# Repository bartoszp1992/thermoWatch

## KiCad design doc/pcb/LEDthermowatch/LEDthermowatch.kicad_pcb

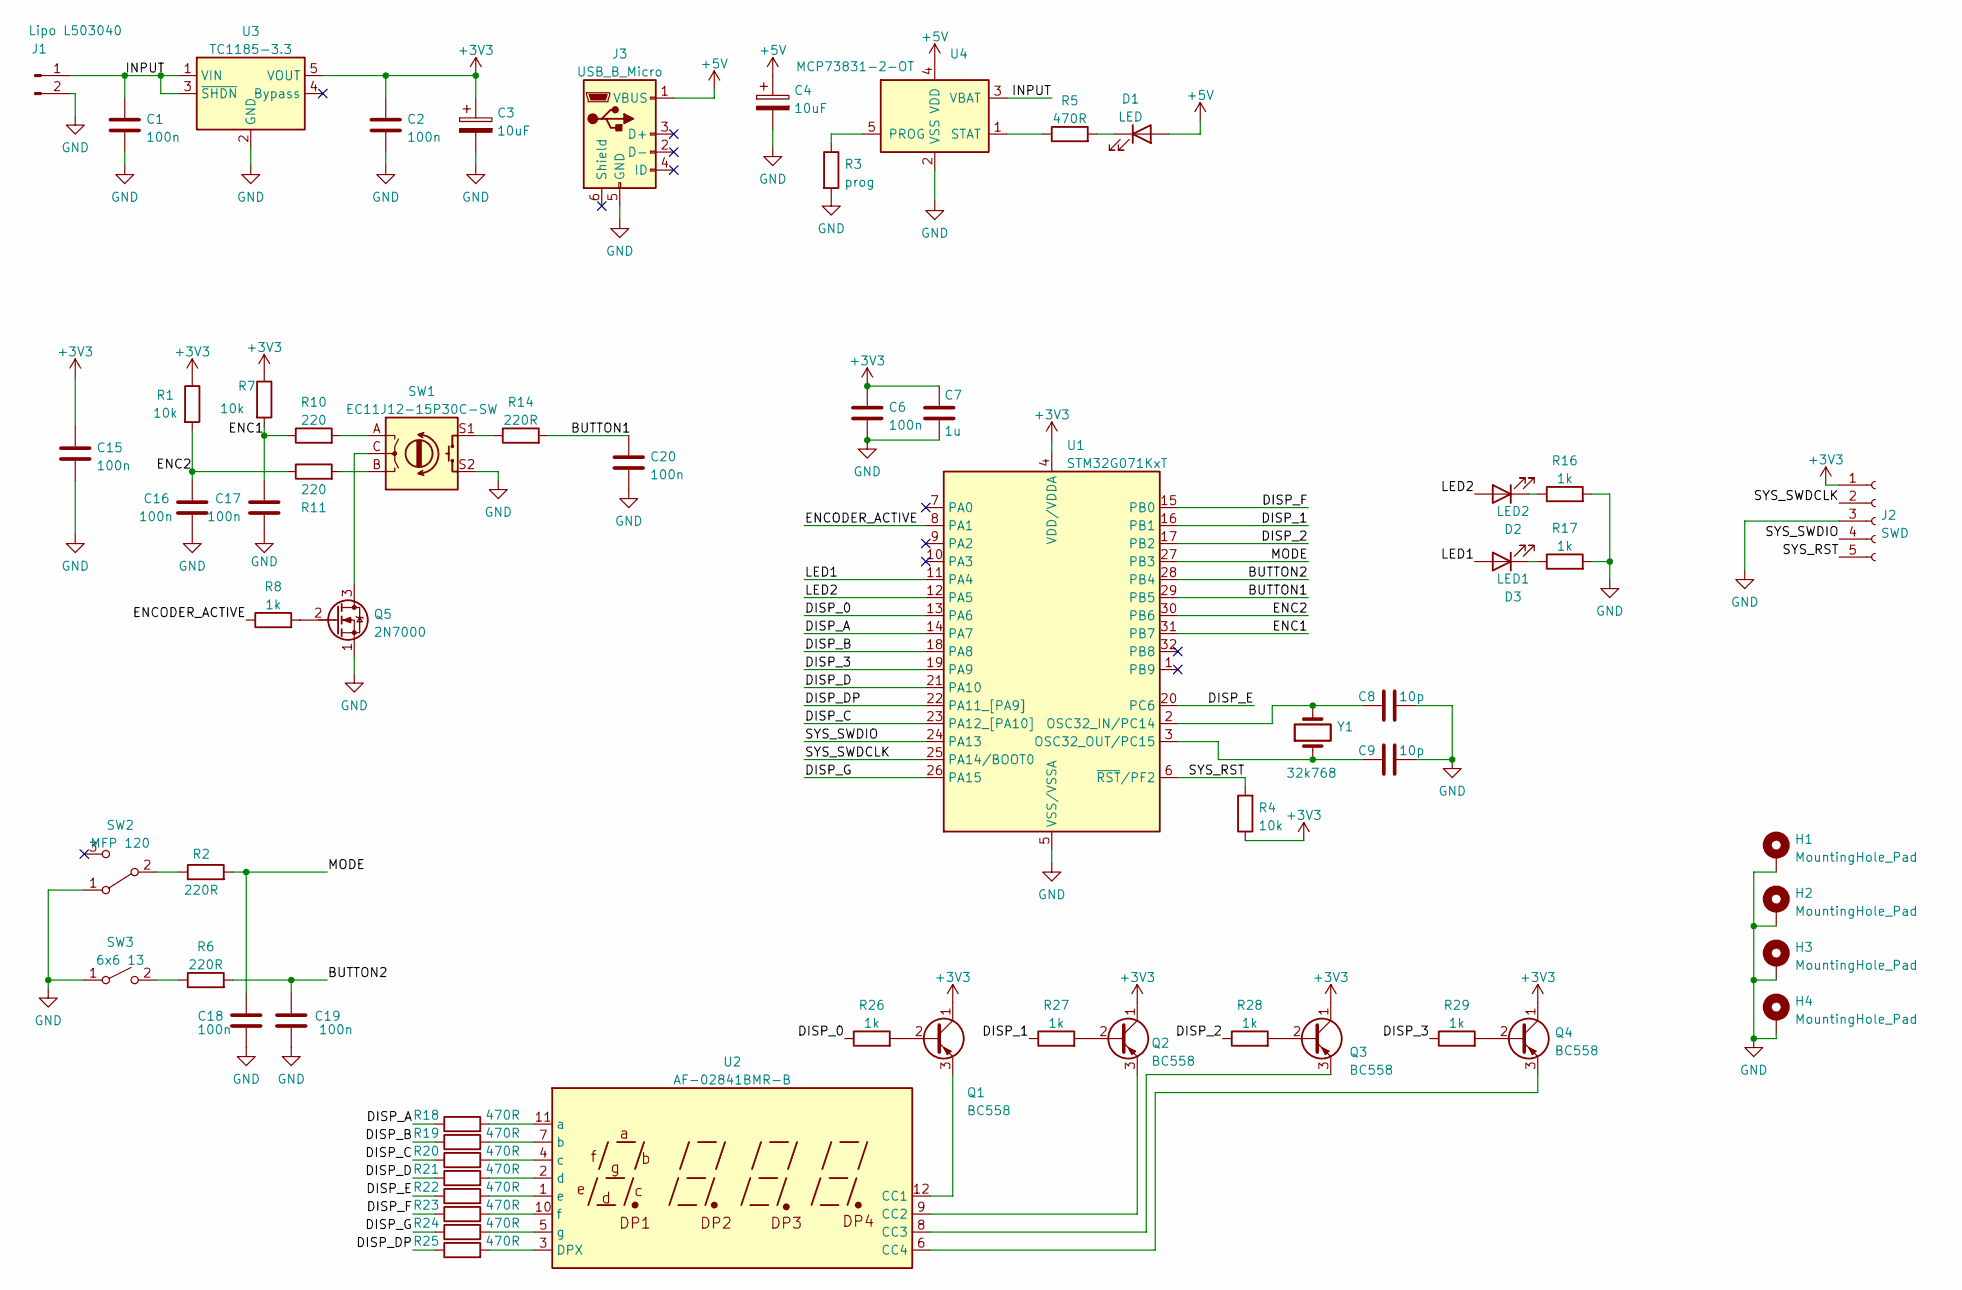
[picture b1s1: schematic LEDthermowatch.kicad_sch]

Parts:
C1, C2, C6, C15, C16, C17, C18, C19, C20: 100n; C_0805_2012Metric
C3, C4: 10uF; CP_Radial_D6.3mm_P2.50mm
C7: 1u; CP_Radial_D6.3mm_P2.50mm
C8, C9: 10p; C_0805_2012Metric
D1: LED; LED_0805_2012Metric
D2: LED2; LED_0805_2012Metric
D3: LED1; LED_0805_2012Metric
H1, H2, H3, H4: MountingHole_Pad; WirePad 4mm^2 Rect
J1: Lipo L503040; CELLEVIA 30x40mm
J2: SWD; PinHeader_1x05_P2.54mm_Vertical
J3: USB_B_Micro; USB_Micro-B_Molex_47346-0001
Q1, Q2, Q3, Q4: BC558; TO-92
Q5: 2N7000; TO-92
R1, R4, R7: 10k; R_Axial_DIN0207_L6.3mm_D2.5mm_P10.16mm_Horizontal
R2, R6, R14: 220R; R_Axial_DIN0207_L6.3mm_D2.5mm_P10.16mm_Horizontal
R3: prog; R_Axial_DIN0207_L6.3mm_D2.5mm_P10.16mm_Horizontal
R5: 470R; R_Axial_DIN0207_L6.3mm_D2.5mm_P10.16mm_Horizontal
R8, R16, R17, R26, R27, R28, R29: 1k; R_Axial_DIN0207_L6.3mm_D2.5mm_P10.16mm_Horizontal
R10, R11: 220; R_Axial_DIN0207_L6.3mm_D2.5mm_P10.16mm_Horizontal
R18, R19, R20, R21, R22, R23, R24, R25: 470R; R_0805_2012Metric
SW1: EC11J12-15P30C-SW
SW2: MFP 120
SW3: 6x6 13; SW_PUSH_6mm_H13mm
U1: STM32G071KxT; LQFP-32_7x7mm_P0.8mm
U2: AF-02841BMR-B; LED 14.2mm
U3: TC1185-3.3; SOT-23-5
U4: MCP73831-2-OT; SOT-23-5
Y1: 32k768; Crystal_D2.00mm_L6.00mm

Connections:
+3V3: C2.1, C3.1, C6.1, C7.1, C15.1, J2.1, Q1.1 (C), Q2.1 (C), Q3.1 (C), Q4.1 (C), R1.1, R4.1, R7.1, U1.4 (VDD/VDDA), U3.5 (VOUT)
+5V: C4.1, D1.2 (A), J3.1 (VBUS), U4.4 (VDD)
/BUTTON1: C20.1, R14.2, U1.29 (PB5)
/BUTTON2: C19.1, R6.2, U1.28 (PB4)
/DISP_0: R26.1, U1.13 (PA6)
/DISP_1: R27.1, U1.16 (PB1)
/DISP_2: R28.1, U1.17 (PB2)
/DISP_3: R29.1, U1.19 (PA9)
/DISP_A: R18.1, U1.14 (PA7)
/DISP_B: R19.1, U1.18 (PA8)
/DISP_C: R20.1, U1.23 (PA12_[PA10])
/DISP_D: R21.1, U1.21 (PA10)
/DISP_DP: R25.1, U1.22 (PA11_[PA9])
/DISP_E: R22.1, U1.20 (PC6)
/DISP_F: R23.1, U1.15 (PB0)
/DISP_G: R24.1, U1.26 (PA15)
/ENC1: C17.1, R7.2, R10.1, U1.31 (PB7)
/ENC2: C16.2, R1.2, R11.1, U1.30 (PB6)
/ENCODER_ACTIVE: R8.1, U1.8 (PA1)
/INPUT: C1.1, J1.1, U3.1 (VIN), U3.3 (~SHDN), U4.3 (VBAT)
/LED1: D3.2 (A), U1.11 (PA4)
/LED2: D2.2 (A), U1.12 (PA5)
/MODE: C18.1, R2.2, U1.27 (PB3)
/SYS_RST: J2.5, R4.2, U1.6 (~RST/PF2)
/SYS_SWDCLK: J2.2, U1.25 (PA14/BOOT0)
/SYS_SWDIO: J2.4, U1.24 (PA13)
GND: C1.2, C2.2, C3.2, C4.2, C6.2, C7.2, C8.2, C9.2, C15.2, C16.1, C17.2, C18.2, C19.2, C20.2, H1.1, H2.1, H3.1, H4.1, J1.2, J2.3, J3.5 (GND), Q5.1 (S), R3.2, R16.2, R17.2, SW1.S2, SW2.1 (A), SW3.1 (A), U1.5 (VSS/VSSA), U3.2 (GND), U4.2 (VSS)
unnamed: C8.1, U1.2 (OSC32_IN/PC14), Y1.2
unnamed: C9.1, U1.3 (OSC32_OUT/PC15), Y1.1
unnamed: D1.1 (K), R5.2
unnamed: D2.1 (K), R16.1
unnamed: D3.1 (K), R17.1
unnamed: Q1.2 (B), R26.2
unnamed: Q1.3 (E), U2.12 (CC1)
unnamed: Q2.2 (B), R27.2
unnamed: Q2.3 (E), U2.9 (CC2)
unnamed: Q3.2 (B), R28.2
unnamed: Q3.3 (E), U2.8 (CC3)
unnamed: Q4.2 (B), R29.2
unnamed: Q4.3 (E), U2.6 (CC4)
unnamed: Q5.2 (G), R8.2
unnamed: Q5.3 (D), SW1.C
unnamed: R2.1, SW2.2 (B)
unnamed: R3.1, U4.5 (PROG)
unnamed: R5.1, U4.1 (STAT)
unnamed: R6.1, SW3.2 (B)
unnamed: R10.2, SW1.A
unnamed: R11.2, SW1.B
unnamed: R14.1, SW1.S1
unnamed: R18.2, U2.11 (a)
unnamed: R19.2, U2.7 (b)
unnamed: R20.2, U2.4 (c)
unnamed: R21.2, U2.2 (d)
unnamed: R22.2, U2.1 (e)
unnamed: R23.2, U2.10 (f)
unnamed: R24.2, U2.5 (g)
unnamed: R25.2, U2.3 (DPX)

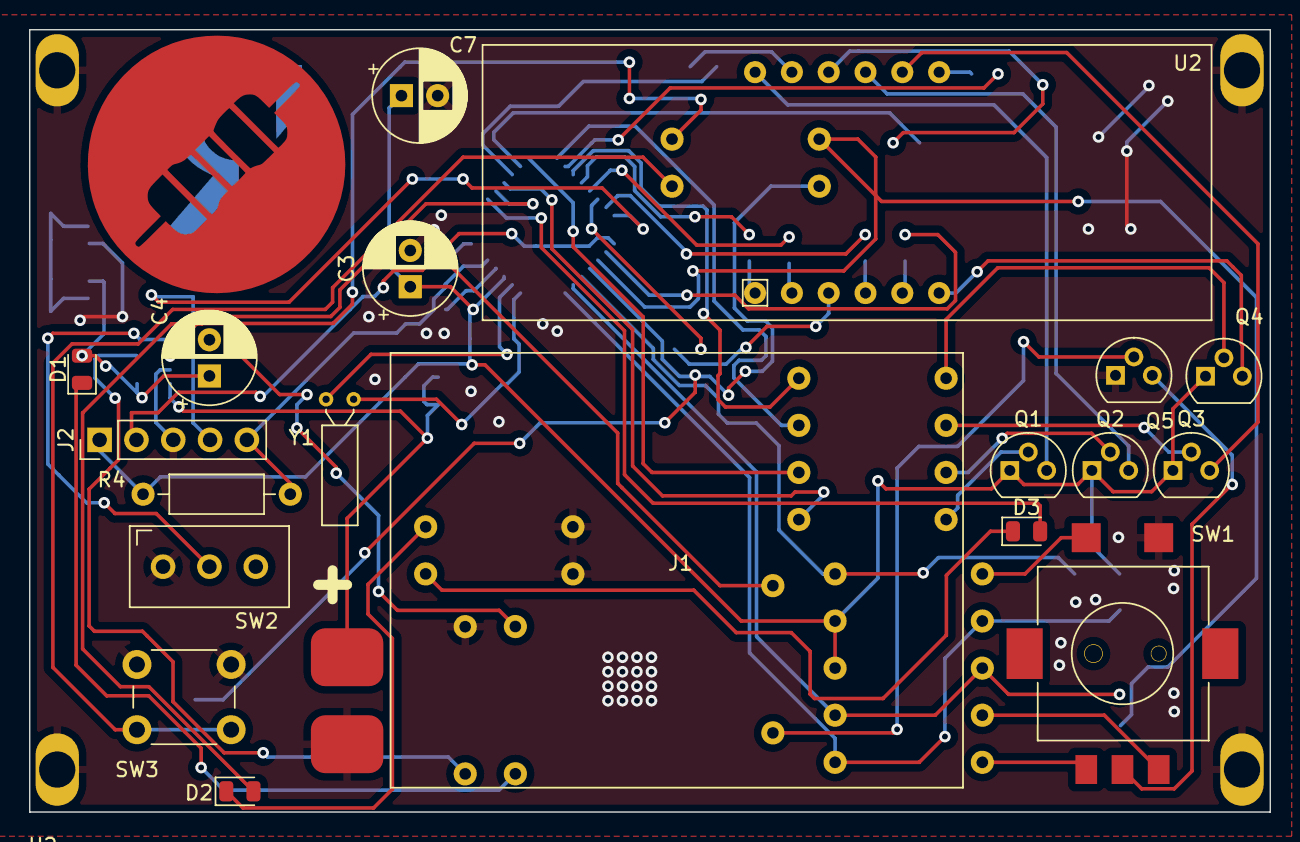
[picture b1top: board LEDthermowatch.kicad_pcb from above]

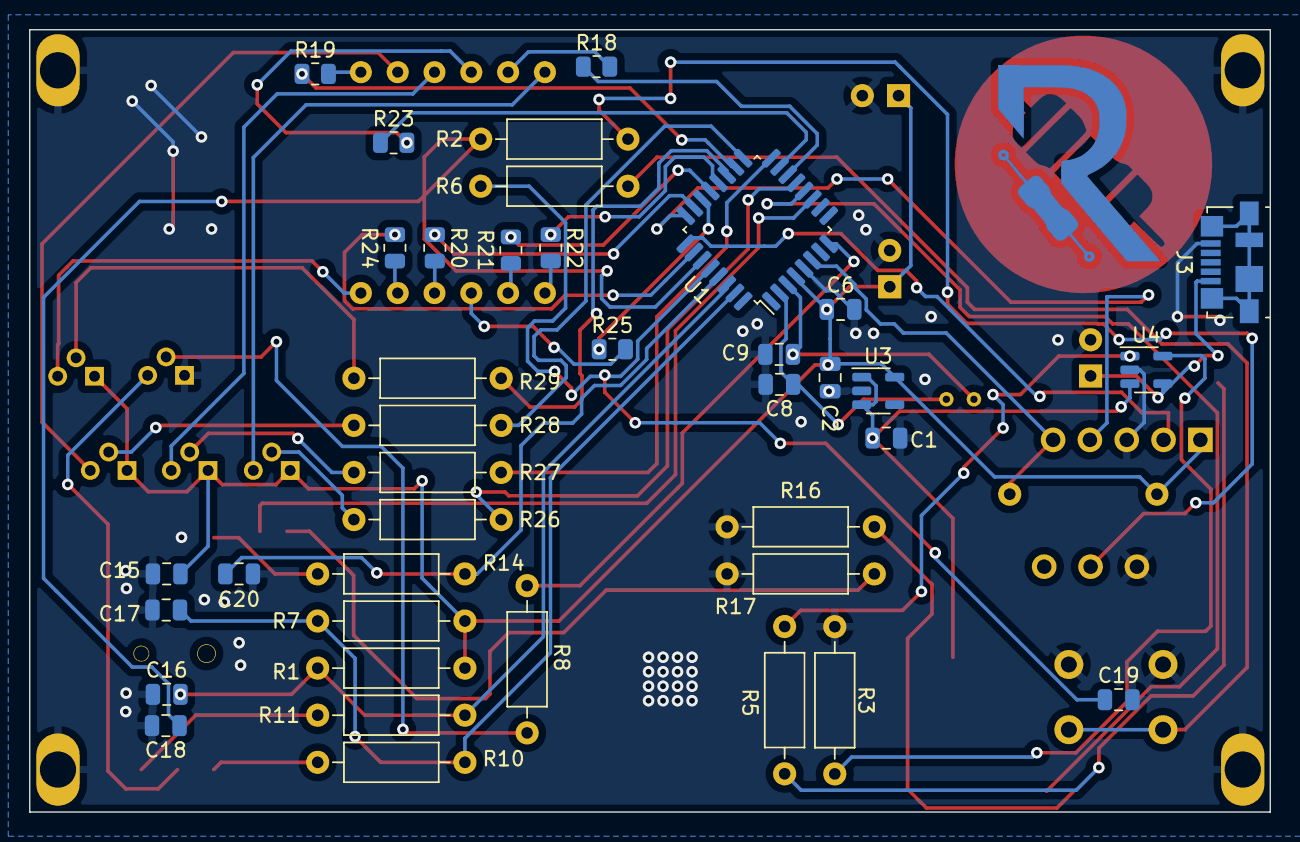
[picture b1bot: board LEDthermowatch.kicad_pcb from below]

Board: 2 copper layers, 85.6 x 54.0 mm, 62 parts (39 on the bottom side), 57 nets.

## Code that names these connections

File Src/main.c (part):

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	bme280.pressureReference = 1013;

//												DISPLAY PIN ASSIGNMENT
	LEDinit(&display, DISP_0_GPIO_Port, DISP_0_Pin, DISP_1_GPIO_Port,
	DISP_1_Pin,
	DISP_2_GPIO_Port, DISP_2_Pin, DISP_3_GPIO_Port, DISP_3_Pin,
	DISP_A_GPIO_Port, DISP_A_Pin, DISP_B_GPIO_Port, DISP_B_Pin,
	DISP_C_GPIO_Port, DISP_C_Pin, DISP_D_GPIO_Port, DISP_D_Pin,
	DISP_E_GPIO_Port, DISP_E_Pin, DISP_F_GPIO_Port, DISP_F_Pin,
	DISP_G_GPIO_Port, DISP_G_Pin, DISP_DP_GPIO_Port, DISP_DP_Pin);

	LEDseparator(&display, "    ");

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
	bme280Init(&bme280, &hi2c1);
	lis3mdlInit(&lis3mdl, &hi2c1);
	HAL_GPIO_WritePin(ENCODER_ACTIVE_GPIO_Port, ENCODER_ACTIVE_Pin, 1);
	HAL_Delay(20);
	menuResetCurrent(&menu);

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  __HAL_RCC_GPIOA_CLK_ENABLE();

  /*Configure GPIO pin Output Level */
  HAL_GPIO_WritePin(GPIOA, ENCODER_ACTIVE_Pin|LED_STANDBY_Pin|LED_WRITE_Pin, GPIO_PIN_RESET);

  /*Configure GPIO pin Output Level */
  HAL_GPIO_WritePin(GPIOA, DISP_0_Pin|DISP_A_Pin|DISP_B_Pin|DISP_3_Pin
                          |DISP_D_Pin|DISP_DP_Pin|DISP_C_Pin|DISP_G_Pin, GPIO_PIN_SET);

  /*Configure GPIO pin Output Level */
  HAL_GPIO_WritePin(GPIOB, DISP_F_Pin|DISP_1_Pin|DISP_2_Pin, GPIO_PIN_SET);

  /*Configure GPIO pin Output Level */
  HAL_GPIO_WritePin(DISP_E_GPIO_Port, DISP_E_Pin, GPIO_PIN_SET);

  /*Configure GPIO pin : BACKUP_Pin */
  GPIO_InitStruct.Pin = BACKUP_Pin;
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  GPIO_InitStruct.Pull = GPIO_NOPULL;
  HAL_GPIO_Init(BACKUP_GPIO_Port, &GPIO_InitStruct);

  /*Configure GPIO pins : ENCODER_ACTIVE_Pin LED_STANDBY_Pin LED_WRITE_Pin DISP_0_Pin
                           DISP_A_Pin DISP_B_Pin DISP_3_Pin DISP_D_Pin
                           DISP_DP_Pin DISP_C_Pin DISP_G_Pin */
  GPIO_InitStruct.Pin = ENCODER_ACTIVE_Pin|LED_STANDBY_Pin|LED_WRITE_Pin|DISP_0_Pin
                          |DISP_A_Pin|DISP_B_Pin|DISP_3_Pin|DISP_D_Pin
                          |DISP_DP_Pin|DISP_C_Pin|DISP_G_Pin;
  GPIO_InitStruct.Mode = GPIO_MODE_OUTPUT_PP;
  GPIO_InitStruct.Pull = GPIO_NOPULL;
  GPIO_InitStruct.Speed = GPIO_SPEED_FREQ_LOW;
  HAL_GPIO_Init(GPIOA, &GPIO_InitStruct);

  /*Configure GPIO pins : DISP_F_Pin DISP_1_Pin DISP_2_Pin */
  GPIO_InitStruct.Pin = DISP_F_Pin|DISP_1_Pin|DISP_2_Pin;
  GPIO_InitStruct.Mode = GPIO_MODE_OUTPUT_PP;
  GPIO_InitStruct.Pull = GPIO_NOPULL;
  GPIO_InitStruct.Speed = GPIO_SPEED_FREQ_LOW;
  HAL_GPIO_Init(GPIOB, &GPIO_InitStruct);

  /*Configure GPIO pin : DISP_E_Pin */
  GPIO_InitStruct.Pin = DISP_E_Pin;
  GPIO_InitStruct.Mode = GPIO_MODE_OUTPUT_PP;
  GPIO_InitStruct.Pull = GPIO_NOPULL;
  GPIO_InitStruct.Speed = GPIO_SPEED_FREQ_LOW;
  HAL_GPIO_Init(DISP_E_GPIO_Port, &GPIO_InitStruct);

  /*Configure GPIO pin : MODE_Pin */
  GPIO_InitStruct.Pin = MODE_Pin;
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  GPIO_InitStruct.Pull = GPIO_PULLUP;
  HAL_GPIO_Init(MODE_GPIO_Port, &GPIO_InitStruct);

  /*Configure GPIO pins : BUTTON2_Pin BUTTON1_Pin */
  GPIO_InitStruct.Pin = BUTTON2_Pin|BUTTON1_Pin;
  GPIO_InitStruct.Mode = GPIO_MODE_IT_FALLING;
  GPIO_InitStruct.Pull = GPIO_PULLUP;
  HAL_GPIO_Init(GPIOB, &GPIO_InitStruct);

  /*Configure GPIO pins : ENC1_Pin ENC2_Pin */
  GPIO_InitStruct.Pin = ENC1_Pin|ENC2_Pin;
  GPIO_InitStruct.Mode = GPIO_MODE_IT_RISING_FALLING;
  GPIO_InitStruct.Pull = GPIO_NOPULL;
  HAL_GPIO_Init(GPIOB, &GPIO_InitStruct);
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	HAL_TIM_Base_Stop_IT(&htim1);
	LEDclear(&display);
	flags[FLAG_SLEEP] = 0;
	HAL_GPIO_WritePin(ENCODER_ACTIVE_GPIO_Port, ENCODER_ACTIVE_Pin, 0);
	HAL_Delay(10);
	HAL_GPIO_WritePin(LED_WRITE_GPIO_Port, LED_WRITE_Pin, 0);
	HAL_GPIO_WritePin(LED_STANDBY_GPIO_Port, LED_STANDBY_Pin, 0);
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
void LPwakeUp(void) {
	SystemClock_Config();
	HAL_GPIO_WritePin(ENCODER_ACTIVE_GPIO_Port, ENCODER_ACTIVE_Pin, 1);
	HAL_Delay(10);
	menuResetCurrent(&menu);
	flags[FLAG_LOCKED] = 0;
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
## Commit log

2022-07-29 schematic only
2022-08-24 drawn PCB

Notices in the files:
Src/main.c:
Copyright (c) 2022 STMicroelectronics.
All rights reserved.
This software is licensed under terms that can be found in the LICENSE file
